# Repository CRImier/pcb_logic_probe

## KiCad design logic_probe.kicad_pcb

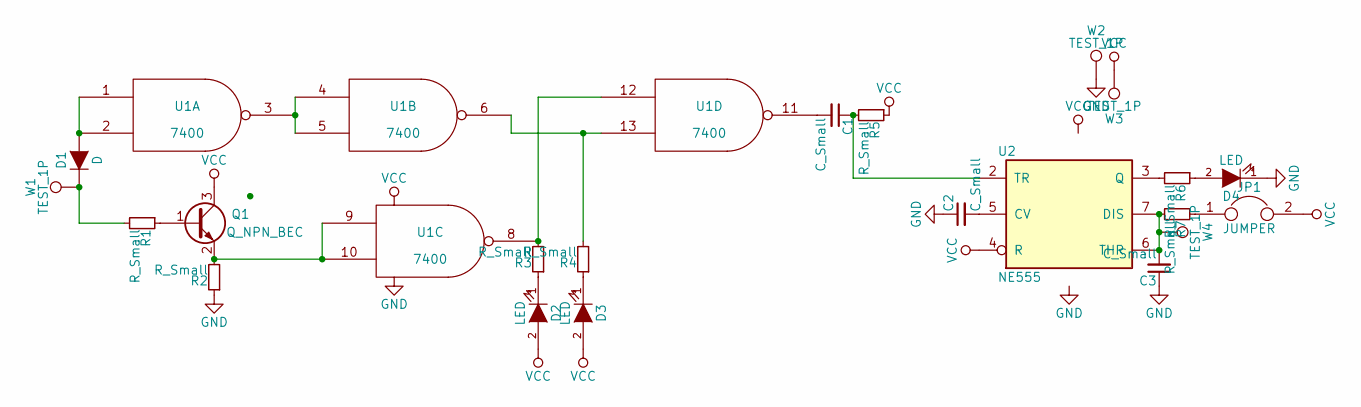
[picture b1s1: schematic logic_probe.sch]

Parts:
C1, C2, C3: C_Small; C_0603_HandSoldering
D1: D; D_0805
D2, D3, D4: LED; D_0603
JP1: JUMPER; GS2
Q1: Q_NPN_BEC; SOT-23_Handsoldering
R1, R2, R3, R4, R5, R6, R7: R_Small; R_0603_HandSoldering
U1: 7400; SOIC-14_3.9x8.7mm_Pitch1.27mm
U2: NE555; SOIC-8_3.9x4.9mm_Pitch1.27mm
W1, W2, W3: TEST_1P; Pin_Header_Angled_1x01_Pitch2.54mm
W4: TEST_1P; Measurement_Point_Round-SMD-Pad_Small

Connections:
GND: C2.1, C3.1, D4.1 (K), R2.1, U1.7 (GND), U2.1 (GND), W2.1
unnamed: C1.1, R5.2, U2.2 (TR)
unnamed: C1.2, U1.11
unnamed: C2.2, U2.5 (CV)
unnamed: C3.2, R7.2, U2.6 (THR), U2.7 (DIS), W4.1
unnamed: D1.1 (K), R1.2, W1.1
unnamed: D1.2 (A), U1.1, U1.2
unnamed: D2.1 (K), R3.1
unnamed: D3.1 (K), R4.1
unnamed: D4.2 (A), R6.1
unnamed: JP1.1, R7.1
unnamed: Q1.1 (B), R1.1
unnamed: Q1.2 (E), R2.2, U1.9, U1.10
unnamed: R3.2, U1.8, U1.12
unnamed: R4.2, U1.6, U1.13
unnamed: R6.2, U2.3 (Q)
unnamed: U1.3, U1.4, U1.5
VCC: D2.2 (A), D3.2 (A), JP1.2, Q1.3 (C), R5.1, U1.14 (VCC), U2.4 (R), U2.8 (VCC), W3.1

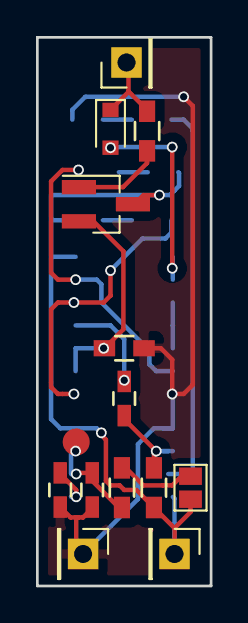
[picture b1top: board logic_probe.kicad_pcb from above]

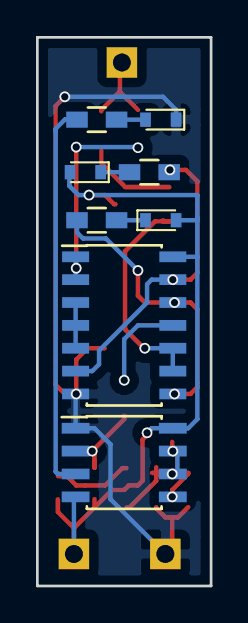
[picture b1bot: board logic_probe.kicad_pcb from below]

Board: 2 copper layers, 9.7 x 30.5 mm, 22 parts (8 on the bottom side), 18 nets.

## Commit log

2017-05-09 :neckbeard: Added .gitattributes & .gitignore files
2017-05-09 Added logic probe PCB files
2017-05-09 Added logic probe gerber files
